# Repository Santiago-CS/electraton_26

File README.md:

# Be Key ITESO Racing Team — Electrical & Embedded Systems

Repositorio central del área de electrónica, sistemas de baja tensión, telemetría y software embebido de **Be Key ITESO Racing Team**, escudería representativa del ITESO en el campeonato nacional **Electratón**.

Este espacio almacena el diseño de hardware (esquemáticos, layouts y archivos de manufactura Gerber/BOM), firmware de unidades de control, protocolos de comunicación en red vehicular e interfaces de adquisición de datos.

---

## 🏎️ Visión General de la Arquitectura

El sistema eléctrico del monoplaza opera bajo una estricta segregación galvánica y funcional entre dos dominios:

1. **Sistema de Alta Tensión (HV - High Voltage):**
   * Banco de celdas de tracción, interruptor general de aislamiento, fusibles de alta corriente y contactores principales.
   * Sistema de Gestión de Baterías (BMS) encargado del balanceo pasivo/activo, monitorización de temperatura por celda y corte seguro ante contingencias.
2. **Sistema de Baja Tensión y Control (LV - Low Voltage):**
   * Lógica de encendido de tracción condicionada a seguridades (*Interlocks*, paro de emergencia/kill switches y frenado hidráulico).
   * Red de comunicación de control y telemetría de parámetros en tiempo real hacia pits.
   * Procesamiento de datos de dinámica, ergonomía e instrumentación del habitáculo del piloto.

---

## 📁 Estructura del Repositorio

```text
├── FRDM-iMX93/
│   ├── 3D Printed Enclosure for FRDM-IMX93/
│   └── FRDM-IMX93-DESIGNFILES/
│       ├── 3D Module/
│       ├── Design Files/
│       ├── Gerbers/
│       └── PDF/
├── docs/                   # Diagramas generales de cableado (harness), pinouts y notas técnicas
├── firmware/               # Proyectos de código fuente embebido (C / C++ / MicroPython)
│   ├── ecu_firmware/       # Lógica principal de tracción y máquina de estados del auto
│   └── wheel_firmware/     # Control del volante, display gráfico e interfaz de mando
├── hardware/               # Diseños electrónicos (Archivos de diseño CAD/EDA, BOMs, Gerbers)
│   ├── ecu/                # PCB de la Unidad de Control del Vehículo (ECU)
│   └── steering_wheel/     # PCB de mandos del volante ergonómico y display de telemetría
└── tools/                  # Scripts de procesamiento, telemetría y configuración en pista
```

---

## 🛠️ Subsistemas de Hardware (Hardware Directory)

### 1. `FRDM-iMX93/`
* **Función:** Plataforma de cómputo embebido y adquisición de datos basada en el procesador NXP i.MX93, empleada para telemetría avanzada, procesamiento y soporte de computación a bordo.
* **Carpetas del módulo:**
  * `3D Printed Enclosure for FRDM-IMX93/`: Archivos de diseño y modelos del gabinete / case para manufactura aditiva y montaje en el chasis.
  * `FRDM-IMX93-DESIGNFILES/`: Archivos de diseño originales de la tarjeta de desarrollo (`3D Module/`, `Design Files/`, `Gerbers/`, `PDF/`).

### 2. `hardware/steering_wheel/`
* **Función:** Módulo de interfaz hombre-máquina (HMI) ubicado en el volante del monoplaza.
* **Componentes Clave:** 
  * Microcontrolador para adquisición de comandos del piloto (pulsadores, selectores rotativos y palancas de cambios/frenado regenerativo).
  * Pantalla gráfica/dashboard integrada para visualización de parámetros críticos en pista (voltaje total, corriente instantánea, velocidad y alarmas del BMS).
  * Comunicación inalámbrica o bus alámbrico hacia la ECU central.
* **Entregables en carpeta:**
  * Esquemáticos y PCB Layout.
  * Archivos Gerber de fabricación y ensamble (CPL/Pick and Place).
  * Lista de materiales (BOM) con números de parte y encapsulados.

### 3. `hardware/ecu/`
* **Función:** Unidad de Control Electrónico encargada de la lógica central del monoplaza y la máquina de estados de seguridad.
* **Componentes Clave:**
  * Microcontrolador principal de gestión en tiempo real.
  * Etapa de acondicionamiento de señales y lectura de sensores analógicos/digitales (posición del pedal de aceleración, presión de frenos, efecto Hall).
  * Drivers y relevadores para control de contactores de potencia y luces reglamentarias de estado (Tractive System Active Light).
  * Circuito de detección de fallas y enlace directo con la línea de paro de emergencia (*Shutdown Circuit*).
* **Entregables en carpeta:**
  * Diseño esquemático y diseño de pista multicapa (separación estricta de planos analógicos y digitales).
  * Archivos de manufactura listos para ensamble y fabricación de PCB.
  * Documentación de conectores y asignación de pines del arnés vehicular.

---

## 🌿 Flujo de Trabajo con Git y Creación de Pull Requests (PR)

Un **Pull Request (PR)** es una solicitud formal para que los líderes del área técnica revisen, validen y aprueben tus cambios antes de mezclarlos con el trabajo de los demás. **Nadie sube cambios directos a la rama `main`.**

### 1. Estructura de Ramas Base
* `main`: Producción oficial. Exclusiva para diseños probados y versiones finales enviadas a manufactura.
* `hardware/dev`: Rama base donde se integran los cambios de circuitos, esquemáticos, PCBs y librerías EDA.
* `firmware/dev`: Rama base para integración de código fuente embebido y librerías de control.
* `tools/dev`: Rama base para scripts de telemetría en pista, procesamiento de datos y utilidades de configuración.
* `docs/general`: Rama base para manuales de taller, diagramas de arnés, pinouts y notas técnicas.

---

### 2. Flujo Completo por Terminal

#### Paso 1: Clonar y actualizar el repositorio local
```bash
git clone <URL_DEL_REPOSITORIO>
cd <NOMBRE_DEL_REPO>
git fetch --all
```

#### Paso 2: Crear tu rama personal de trabajo
Sitúate en la rama base de tu disciplina y crea una rama específica para tu tarea:

* **Si vas a diseñar hardware (esquemático/PCB):**
```bash
git checkout hardware/dev
git pull origin hardware/dev
git checkout -b hardware/nombre-tarea
# Ejemplo: git checkout -b hardware/filtro-alimentacion-ecu
```

* **Si vas a programar firmware:**
```bash
git checkout firmware/dev
git pull origin firmware/dev
git checkout -b firmware/nombre-tarea
# Ejemplo: git checkout -b firmware/lectura-pedal-adc
```

* **Si vas a desarrollar scripts / herramientas / telemetría:**
```bash
git checkout tools/dev
git pull origin tools/dev
git checkout -b tools/nombre-tarea
# Ejemplo: git checkout -b tools/parser-telemetria-serial
```

* **Si vas a actualizar documentación o diagramas:**
```bash
git checkout docs/general
git pull origin docs/general
git checkout -b docs/nombre-tarea
# Ejemplo: git checkout -b docs/diagrama-arnes-potencia
```

#### Paso 3: Guardar cambios y crear commits limpios
Agrega únicamente los archivos pertinentes (esquemáticos, código fuente, scripts, modelos 3D). Evita subir archivos temporales, respaldos locales o cachés de compilación:
```bash
git status
git add hardware/ecu/archivo_modificado.kicad_sch
git commit -m "feat(ecu): agregar diodo de proteccion contra polaridad inversa"
```

*Convenciones de mensajes:*
* `feat(módulo):` nueva función, circuito o subsistema.
* `fix(módulo):` corrección de errores, trazos de PCB o bugs de software.
* `docs(módulo):` diagramas de cableado, notas de conexionado o manuales.
* `tools(módulo):` scripts de adquisición, análisis o utilerías de pista.

#### Paso 4: Subir tu rama a GitHub
```bash
git push -u origin <nombre-completo-de-tu-rama>
# Ejemplo: git push -u origin hardware/filtro-alimentacion-ecu
```

---

### 3. Cómo abrir y procesar el Pull Request (PR)

#### Opción A: Desde la interfaz web de GitHub (Método estándar)
1. Entra al enlace del repositorio en GitHub desde tu navegador.
2. Verás un recuadro amarillo con el botón **"Compare & pull request"**. Haz clic ahí. (Si no aparece, entra a la pestaña **Pull requests** y presiona **New pull request**).
3. **Selección de ramas (Punto crítico):**
   * **Base (izquierda):** Selecciona la rama destino según tu área (`hardware/dev`, `firmware/dev`, `tools/dev` o `docs/general`). **No selecciones `main`** a menos que sea una entrega formal de temporada.
   * **Compare (derecha):** Selecciona tu rama de trabajo personal (`hardware/nombre-tarea`, `firmware/nombre-tarea`, etc.).
4. **Título y Descripción:**
   * Título corto y descriptivo: `feat(ecu): Proteccion contra polaridad inversa y desacoplo`.
   * Descripción: Explica qué problema resuelve, qué pruebas realizaste (simulación, osciloscopio o banco de pruebas) y si modificaste algún componente en la BOM.
5. **Revisores:** En la columna lateral derecha, en **Reviewers**, asigna al **Senior Chief Engineer** o al **Capitán de Área Técnica**.
6. Haz clic en **Create pull request**.

#### Opción B: Desde la terminal usando GitHub CLI (`gh`)
Si tienes instalada la herramienta oficial de GitHub en tu consola:
```bash
# Para hardware apuntando a hardware/dev:
gh pr create --base hardware/dev --title "feat(ecu): proteccion inversa" --body "Se agrega diodo y capacitor de desacoplo en entrada de 12V"

# Para firmware apuntando a firmware/dev:
gh pr create --base firmware/dev --title "feat(pedal): calibracion ADC" --body "Lectura lineal de pedal con debounce y promedio movil"

# Para herramientas apuntando a tools/dev:
gh pr create --base tools/dev --title "feat(telemetria): script de lectura serial" --body "Parser de tramas UART y almacenamiento en CSV"

# Para documentación apuntando a docs/general:
gh pr create --base docs/general --title "docs(arnes): pinout conector principal" --body "Actualizacion de diagrama de pines de alimentacion y sensores"
```

#### Paso 5: ¿Qué pasa si te piden correcciones en la revisión?
No cierres el PR ni generes una nueva rama. Aplica las correcciones en tus archivos locales dentro de tu misma rama de trabajo, guarda los cambios y vuelve a enviar el push:
```bash
git add hardware/ecu/archivo_corregido.kicad_sch
git commit -m "fix(ecu): corregir espaciado de pistas segun observaciones"
git push origin <nombre-completo-de-tu-rama>
```
El Pull Request en GitHub se actualizará automáticamente con el nuevo commit. Cuando los revisores den su visto bueno, realizarán el **Merge** formal hacia la rama de desarrollo correspondiente.

---

## 🔒 Protocolos de Seguridad y Trabajo en Taller

Todo trabajo desarrollado en este repositorio debe respetar de forma obligatoria las normas de seguridad del equipo:

1. **Aislamiento Eléctrico:** Antes de conectar cualquier tarjeta o programador al auto, verifique que la etapa de alta tensión se encuentre físicamente desconectada mediante el *Service Plug* y que el bus de potencia esté descargado a menos de 5 V.
2. **Uso de EPP:** Es mandatorio portar calzado de seguridad, bata de laboratorio y lentes normados durante cualquier sesión de soldadura, maquinado o pruebas dinámicas.
3. **Manejo de Baterías:** Queda prohibido intervenir módulos de acumuladores sin guantes dieléctricos y sin extintores adecuados (CO2 / Clase C / F-500) a la mano y despejados.

---

## 📜 Política de Confidencialidad y NDA

Este repositorio contiene información técnica propietaria, sensible y confidencial de **Be Key ITESO Racing Team**:

* Queda estrictamente prohibido clonar, transferir, duplicar, filtrar o exponer estos esquemáticos, diagramas o código a entidades ajenas al proyecto o a otras escuderías de competencia sin un **Convenio de Colaboración e Intercambio Técnico Oficial** firmado por el Team Principal, la Mesa Directiva y avalado por el responsable del PTI de ITESO.
* Cualquier divulgación deliberada o no autorizada causará la apertura inmediata de un expediente disciplinario, la expulsión definitiva del equipo y el escalamiento a las autoridades académicas y al Comité de Ética del ITESO.

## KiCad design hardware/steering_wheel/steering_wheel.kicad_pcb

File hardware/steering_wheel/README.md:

# Steering wheel controller (RW612) — schematic + placement

Hardware for the Electratón 26 steering wheel: an NXP RW612 (Wi-Fi 6 / BLE) controller
driving a 4" LCD, NeoPixels, two encoders and ten buttons, running from a 1S Li-ion pack
with USB-C charging.

**This folder holds the schematic and the board placement. The board is not routed.**

```
source <your venv>/bin/activate
pip install skidl ortools shapely scipy pymupdf scikit-image ezdxf

python steering_wheel.py                  # netlist + KiCad sheets + bom.csv
python tools/check_sch.py                 # re-reads the sheets, checks every pin
python tools/layout_steering.py place     # placement -> build/placed.kicad_pcb
```

Open `steering_wheel.kicad_pro` in KiCad 10 and press **B** to refill the zones.

> The schematic is **generated** by `steering_wheel.py` (SKiDL). Edit that script and
> re-run it — anything changed directly in Eeschema is lost on the next run. Same for the
> placement: it is code in `tools/layout_steering.py`.

> The sheets here are saved in KiCad 10 format. `tools/kicad_sch_export.py` stamps
> regenerated sheets as KiCad 9 (`version 20250114`, lines 461 and 693), so after re-running
> `steering_wheel.py` KiCad 10 will offer to upgrade them again — harmless, or change those
> two lines to `20260306` / `"10.0"` to stop it.

## State

| | |
|---|---|
| Schematic | rev 0.2 — 5 sheets, 237 parts, 152 nets, **ERC 0 violations** |
| Board | **placed, not routed** — 8 layers, JLCPCB `JLC08161H-7628`, 1.6 mm, 138.9 × 83.8 mm |
| Placement copper | 108 tracks / 17 vias, all locked (power loops, USB breakout, battery trunks, RW612 buck and crystal links) |
| DRC (zones filled, `--schematic-parity`) | **0 errors, 0 parity errors, 384 unconnected** |

The 384 unconnected are the connections still to be routed — exactly what a placement-only
board should report.

## Layer stack

| # | Layer | Use |
|---|---|---|
| 1 | F.Cu | parts (all on top), signals, 50 Ω RF microstrip, GND pour |
| 2 | In1.Cu | **GND plane** — RF and USB reference |
| 3 | In2.Cu | signal |
| 4 | In3.Cu | **+3V3 plane** |
| 5 | In4.Cu | **GND plane** |
| 6 | In5.Cu | signal |
| 7 | In6.Cu | **GND plane** |
| 8 | B.Cu | signals, VSYS_SW trunk, GND pour |

Four routing layers, each against a ground plane. Vias are 0.4/0.2 mm, BGA fan-out
0.35/0.2 mm (8.01:1 aspect ratio — no small-via option needed).

## Routing it

The routing pipeline is not in this folder. A **fully routed** 8-layer version of this same
design (0 DRC errors, 0 parity errors) lives in `~/projects/irt/steering_wheel/pcb_8layer`,
and the 4-layer original in `~/projects/irt/steering_wheel/pcb`. To route from here, copy
`build/env.sh`, `build/run_all.sh`, `build/finalize.sh` and `build/strip_vias.py` from
`pcb_8layer/build/` and fix the paths in `env.sh`.

## Layout

| Path | What |
|---|---|
| `steering_wheel.py` | the design (SKiDL) — **the source of truth** |
| `*.kicad_sch`, `steering_wheel.kicad_pro`, `*-lib-table` | generated KiCad project |
| `steering_wheel.kicad_pcb` | the placed board (copy of `build/placed.kicad_pcb`) |
| `steering_wheel.net`, `bom.csv` | generated netlist and BOM (98 lines, 237 parts, 9 DNP) |
| `lib/` | project symbols and footprints, the stock KiCad symbols used, RW612 ball map |
| `tools/` | schematic export, placement, pre-routing and KiCad-Python helpers |
| `docs/design_notes.md` | **full design documentation** — power tree, pin map, firmware hooks, layout, schematic review, what to check before ordering |
| `docs/PCB_Volante_2026.DXF` | mechanical outline and mounting holes (placement reads this) |
| `docs/pcb_*.png`, `docs/pcb_layers.pdf` | previews of the placed board |
| `build/kicad_netlist.net` | KiCad's own netlist; the board takes no-connect net names from it so DRC parity matches |

## Before ordering

See `docs/design_notes.md` section 7. Two items need a decision:

1. **Q101 (FS8205A) pads 1 and 8** are both the `D12` common-drain pin, which the schematic
   leaves unconnected, so DRC always reports one unconnected item. The usual SOP-8 pinout
   has no drain pin (1,2,3 = S1, 6,7,8 = S2), so the symbol/footprint pin map may be wrong.
2. **The USB pair is ~128 Ω differential, not 90 Ω** on this stackup. ~0.40 mm traces at a
   0.15 mm gap would reach 90 Ω.

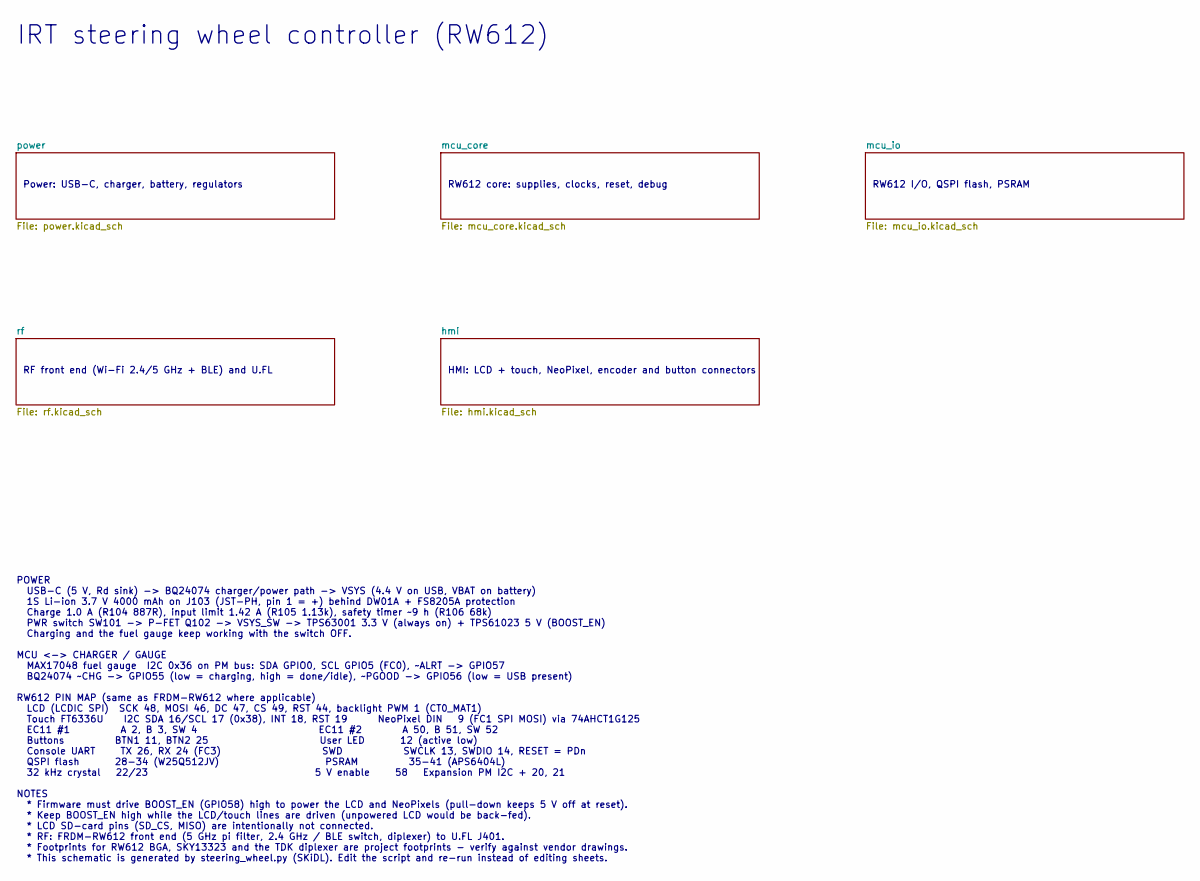
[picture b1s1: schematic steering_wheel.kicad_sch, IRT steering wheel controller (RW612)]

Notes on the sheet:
RW612 I/O, QSPI flash, PSRAM
Power: USB-C, charger, battery, regulators
RW612 core: supplies, clocks, reset, debug
HMI: LCD + touch, NeoPixel, encoder and button connectors
POWER USB-C (5 V, Rd sink) -> BQ24074 charger/power path -> VSYS (4.4 V on USB, VBAT on battery) 1S Li-ion 3.7 V 4000 mAh on J103 (JST-PH, pin 1 = +) behind DW01A + FS8205A protection Charge 1.0 A (R104 887R), input limit 1.42 A (R105 1.13k), safety timer ~9 h (R106 68k) PWR switch SW101 -> P-FET Q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
IRT steering wheel controller (RW612)
RF front end (Wi-Fi 2.4/5 GHz + BLE) and U.FL

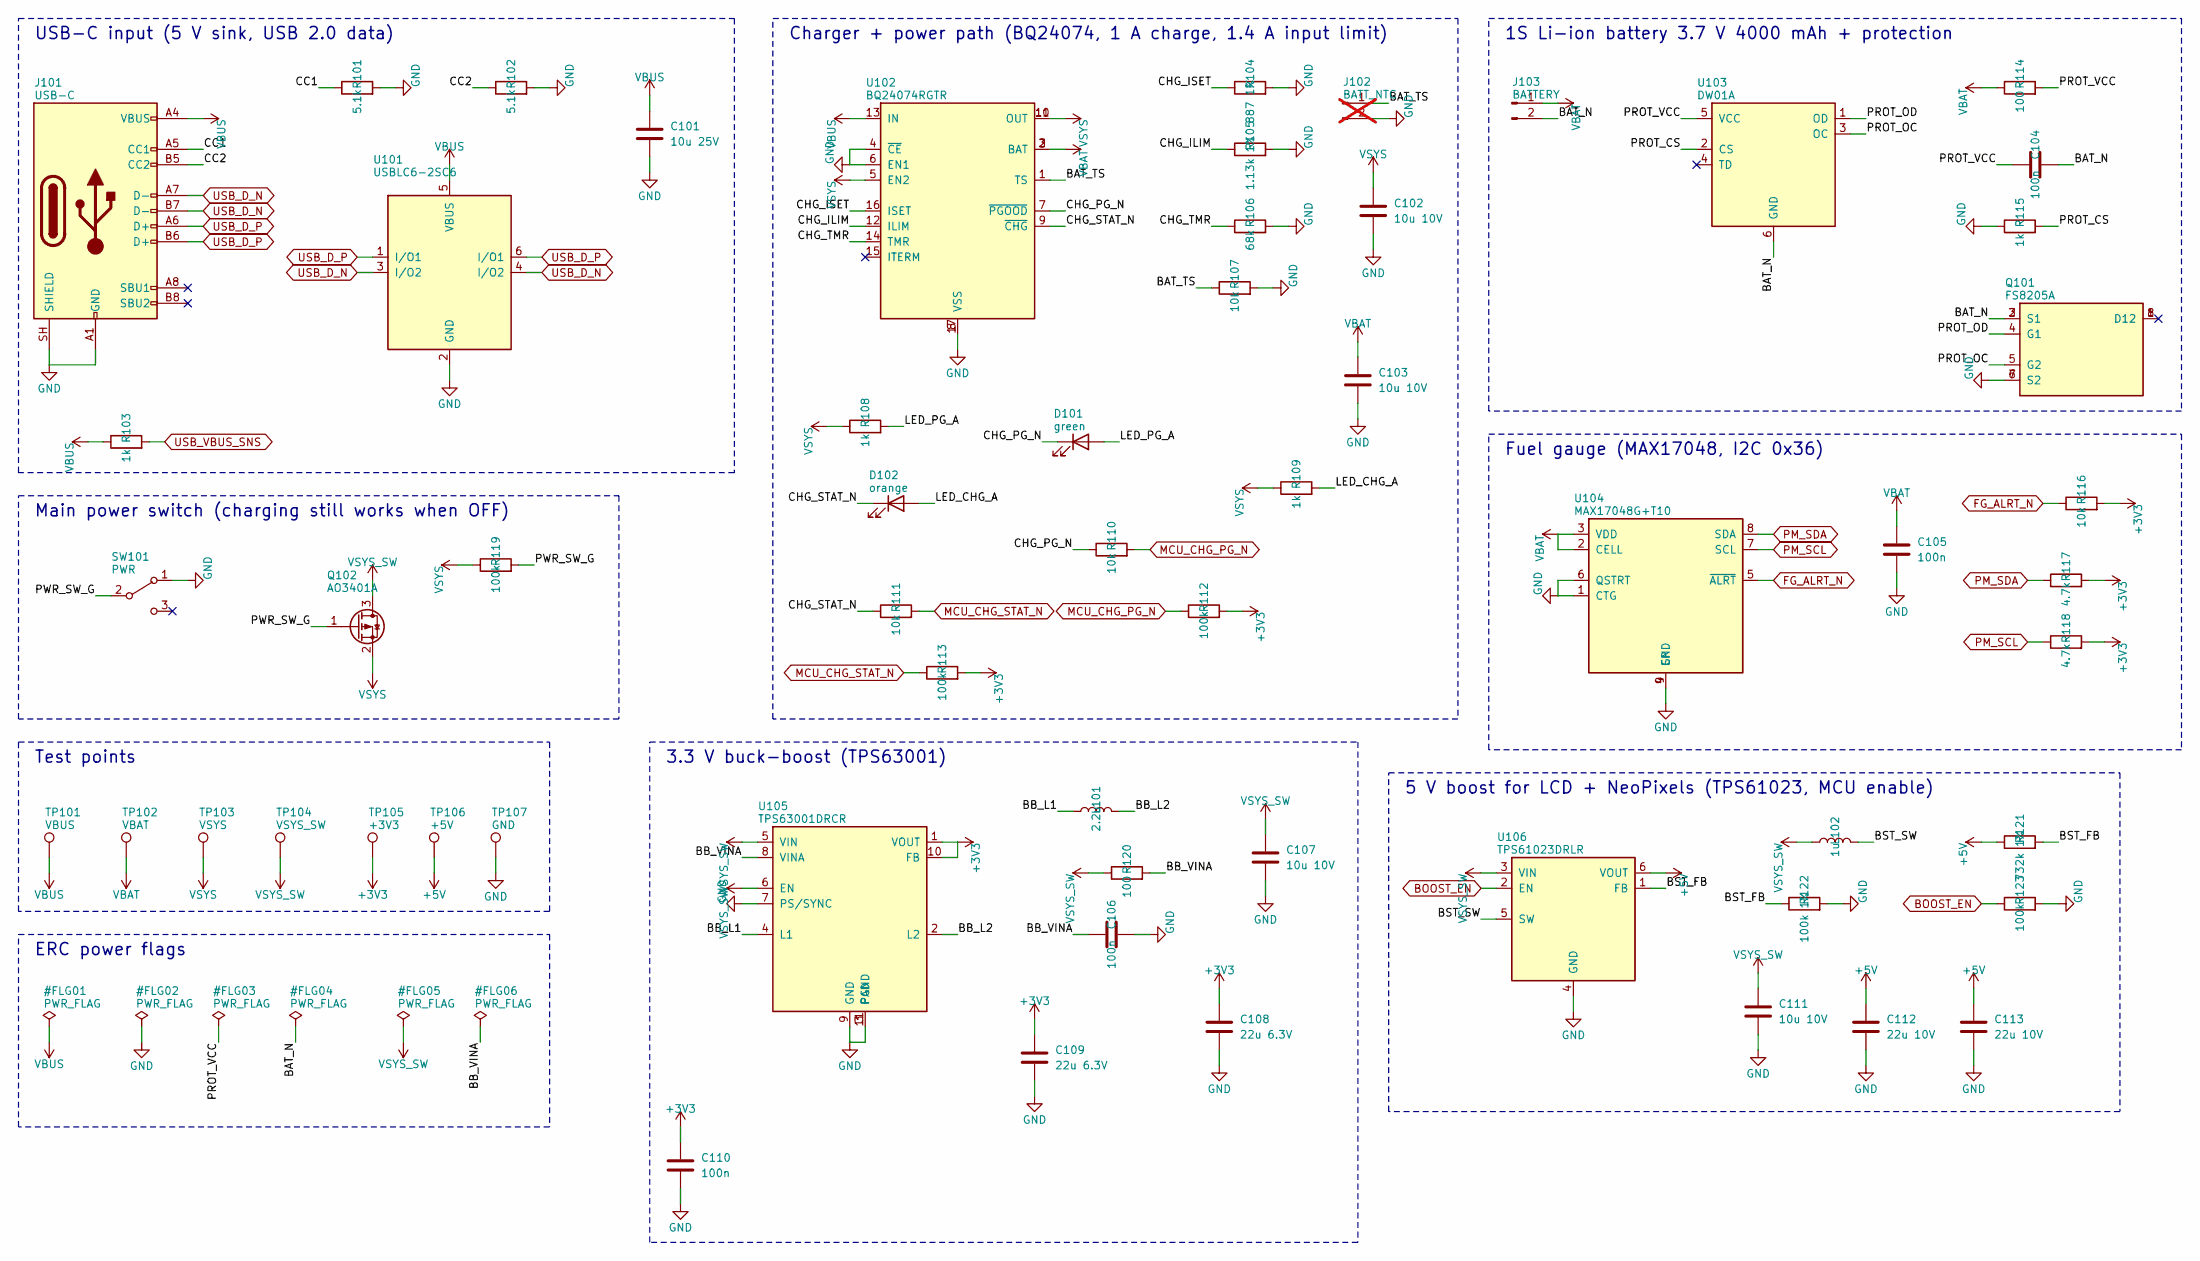
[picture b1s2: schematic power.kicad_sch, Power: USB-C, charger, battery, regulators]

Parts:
C101: 10u 25V; C_0805_2012Metric
C102, C103: 10u 10V; C_0805_2012Metric
C104, C105, C106, C110: 100n; C_0402_1005Metric
C107, C111: 10u 10V; C_0603_1608Metric
C108, C109: 22u 6.3V; C_0805_2012Metric
C112, C113: 22u 10V; C_0805_2012Metric
D101: green; LED_0603_1608Metric; MPN LED green 0603
D102: orange; LED_0603_1608Metric; MPN LED orange 0603
J101: USB-C; USB_C_Receptacle_HRO_TYPE-C-31-M-12; MPN TYPE-C-31-M-12; LCSC C165948
J102: BATT_NTC; PinHeader_1x02_P2.54mm_Vertical; not fitted
J103: BATTERY; JST_PH_S2B-PH-SM4-TB_1x02-1MP_P2.00mm_Horizontal; MPN S2B-PH-SM4-TB; LCSC C295747
L101: 2.2u; L_Wuerth_MAPI-3015; MPN 74438335022
L102: 1u; L_Wuerth_MAPI-4020; MPN 74438357010
Q101: FS8205A; TSSOP-8_4.4x3mm_P0.65mm; MPN FS8205A; LCSC C16052
Q102: AO3401A; SOT-23; MPN AO3401A; LCSC C15127
R101, R102: 5.1k; R_0402_1005Metric
R103, R108, R109, R115: 1k; R_0402_1005Metric
R104: 887 1%; R_0402_1005Metric
R105: 1.13k 1%; R_0402_1005Metric
R106: 68k; R_0402_1005Metric
R107, R110, R111, R116: 10k; R_0402_1005Metric
R112, R113, R119, R123: 100k; R_0402_1005Metric
R114, R120: 100; R_0402_1005Metric
R117, R118: 4.7k; R_0402_1005Metric
R121: 732k 1%; R_0402_1005Metric
R122: 100k 1%; R_0402_1005Metric
SW101: PWR; SW_SPDT_PCM12; MPN PCM12SMTR; LCSC C221841
TP101: VBUS; TestPoint_Pad_D1.0mm
TP102: VBAT; TestPoint_Pad_D1.0mm
TP103: VSYS; TestPoint_Pad_D1.0mm
TP104: VSYS_SW; TestPoint_Pad_D1.0mm
TP105: +3V3; TestPoint_Pad_D1.0mm
TP106: +5V; TestPoint_Pad_D1.0mm
TP107: GND; TestPoint_Pad_D1.0mm
U101: USBLC6-2SC6; SOT-23-6; MPN USBLC6-2SC6; LCSC C7519
U102: BQ24074RGTR; VQFN-16-1EP_3x3mm_P0.5mm_EP1.68x1.68mm; MPN BQ24074RGTR; LCSC C54313
U103: DW01A; SOT-23-6; MPN DW01A; LCSC C351410
U104: MAX17048G+T10; TDFN-8-1EP_2x2mm_P0.5mm_EP0.8x1.2mm; MPN MAX17048G+T10; LCSC C2682616
U105: TPS63001DRCR; VSON-10-1EP_3x3mm_P0.5mm_EP1.65x2.4mm; MPN TPS63001DRCR; LCSC C28060
U106: TPS61023DRLR; SOT-563; MPN TPS61023DRLR; LCSC C919459

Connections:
+3V3: C108.1, C109.1, C110.1, R112.2, R113.2, R116.2, R117.2, R118.2, TP105.1, U105.1 (VOUT), U105.10 (FB); also elsewhere on the board
+5V: C112.1, C113.1, R121.1, TP106.1, U106.6 (VOUT); also elsewhere on the board
/power/BAT_N: C104.2, J103.2, Q101.2 (S1), Q101.3 (S1), U103.6 (GND)
/power/BAT_TS: J102.1, R107.1, U102.1 (TS)
/power/BB_L1: L101.1, U105.4 (L1)
/power/BB_L2: L101.2, U105.2 (L2)
/power/BB_VINA: C106.1, R120.2, U105.8 (VINA)
/power/BST_FB: R121.2, R122.1, U106.1 (FB)
/power/BST_SW: L102.2, U106.5 (SW)
/power/CC1: J101.A5 (CC1), R101.1
/power/CC2: J101.B5 (CC2), R102.1
/power/CHG_ILIM: R105.1, U102.12 (ILIM)
/power/CHG_ISET: R104.1, U102.16 (ISET)
/power/CHG_PG_N: D101.1 (K), R110.1, U102.7 (~PGOOD)
/power/CHG_STAT_N: D102.1 (K), R111.1, U102.9 (~CHG)
/power/CHG_TMR: R106.1, U102.14 (TMR)
/power/LED_CHG_A: D102.2 (A), R109.2
/power/LED_PG_A: D101.2 (A), R108.2
/power/PROT_CS: R115.2, U103.2 (CS)
/power/PROT_OC: Q101.5 (G2), U103.3 (OC)
/power/PROT_OD: Q101.4 (G1), U103.1 (OD)
/power/PROT_VCC: C104.1, R114.2, U103.5 (VCC)
/power/PWR_SW_G: Q102.1 (G), R119.2, SW101.2 (B)
BOOST_EN: R123.1, U106.2 (EN); also elsewhere on the board
FG_ALRT_N: R116.1, U104.5 (~ALRT); also elsewhere on the board
GND: C101.2, C102.2, C103.2, C105.2, C106.2, C107.2, C108.2, C109.2, C110.2, C111.2, C112.2, C113.2, J101.A1 (GND), J101.A12 (GND), J101.B1 (GND), J101.B12 (GND), J101.SH (SHIELD), J102.2, Q101.6 (S2), Q101.7 (S2), R101.2, R102.2, R104.2, R105.2, R106.2, R107.2, R115.1, R122.2, R123.2, SW101.1 (A), TP107.1, U101.2 (GND), U102.4 (~CE), U102.6 (EN1), U102.8 (VSS), U102.17 (VSS), U104.1 (CTG), U104.4 (GND), U104.6 (QSTRT), U104.9 (EP), U105.3 (PGND), U105.7 (PS/SYNC), U105.9 (GND), U105.11 (PAD), U106.4 (GND); also elsewhere on the board
MCU_CHG_PG_N: R110.2, R112.1; also elsewhere on the board
MCU_CHG_STAT_N: R111.2, R113.1; also elsewhere on the board
PM_SCL: R118.1, U104.7 (SCL); also elsewhere on the board
PM_SDA: R117.1, U104.8 (SDA); also elsewhere on the board
USB_D_N: J101.A7 (D-), J101.B7 (D-), U101.3 (I/O2), U101.4 (I/O2); also elsewhere on the board
USB_D_P: J101.A6 (D+), J101.B6 (D+), U101.1 (I/O1), U101.6 (I/O1); also elsewhere on the board
USB_VBUS_SNS: R103.2; also elsewhere on the board
VBAT: C103.1, C105.1, J103.1, R114.1, TP102.1, U102.2 (BAT), U102.3 (BAT), U104.2 (CELL), U104.3 (VDD)
VBUS: C101.1, J101.A4 (VBUS), J101.A9 (VBUS), J101.B4 (VBUS), J101.B9 (VBUS), R103.1, TP101.1, U101.5 (VBUS), U102.13 (IN)
VSYS: C102.1, Q102.2 (S), R108.1, R109.1, R119.1, TP103.1, U102.5 (EN2), U102.10 (OUT), U102.11 (OUT)
VSYS_SW: C107.1, C111.1, L102.1, Q102.3 (D), R120.1, TP104.1, U105.5 (VIN), U105.6 (EN), U106.3 (VIN)

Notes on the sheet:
Test points
Fuel gauge (MAX17048, I2C 0x36)
5 V boost for LCD + NeoPixels (TPS61023, MCU enable)
Charger + power path (BQ24074, 1 A charge, 1.4 A input limit)
1S Li-ion battery 3.7 V 4000 mAh + protection
3.3 V buck-boost (TPS63001)
ERC power flags
Main power switch (charging still works when OFF)
USB-C input (5 V sink, USB 2.0 data)

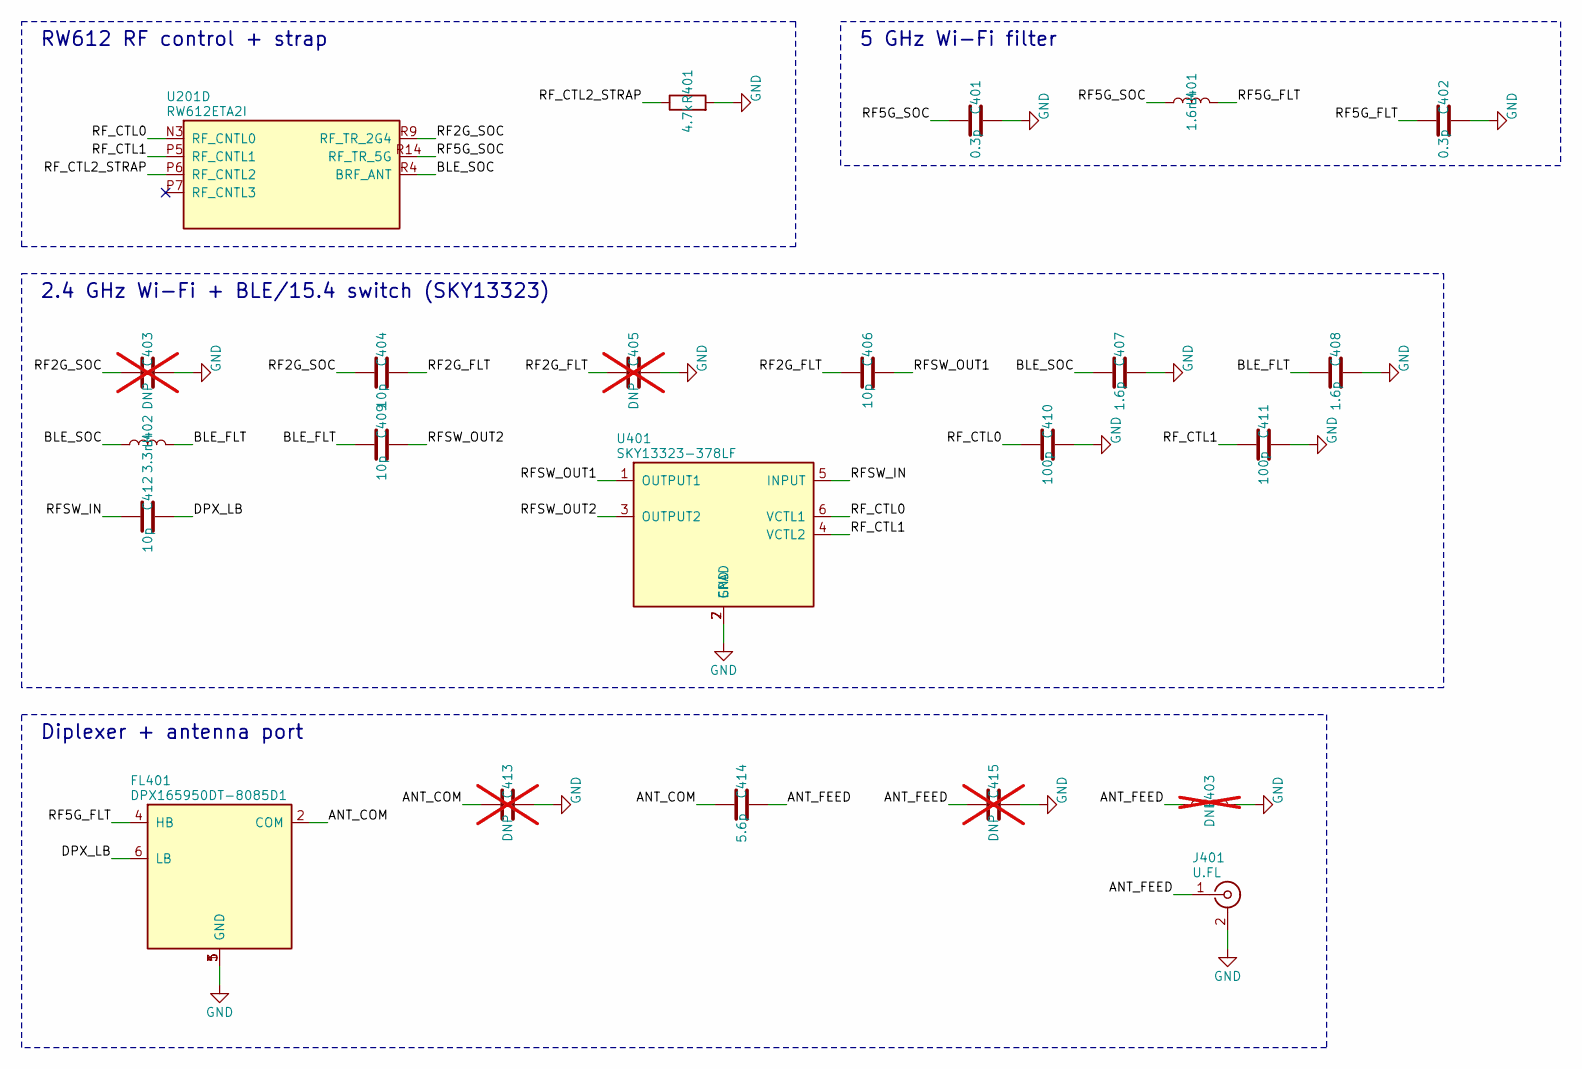
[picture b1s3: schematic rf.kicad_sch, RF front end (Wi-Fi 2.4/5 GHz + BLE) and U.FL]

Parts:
C401, C402: 0.3p; C_0201_0603Metric
C403, C405, C413, C415: DNP; C_0201_0603Metric; not fitted
C404, C406, C409, C412: 10p; C_0201_0603Metric
C407, C408: 1.6p; C_0201_0603Metric
C410, C411: 100p; C_0201_0603Metric
C414: 5.6p; C_0201_0603Metric
FL401: DPX165950DT-8085D1; TDK_DPX165950DT_1608_6T; MPN DPX165950DT-8085D1
J401: U.FL; U.FL_Hirose_U.FL-R-SMT-1_Vertical; MPN U.FL-R-SMT-1(10); LCSC C88373
L401: 1.6nH; L_0201_0603Metric; MPN LQP03TN1N6B02D
L402: 3.3nH; L_0201_0603Metric; MPN LQP03TN3N3B02D
L403: DNP; L_0201_0603Metric; not fitted
R401: 4.7k; R_0402_1005Metric
U201: RW612ETA2I; NXP_TFBGA145_8x8mm_P0.5mm; MPN RW612ETA2I
U401: SKY13323-378LF; Skyworks_MLPD-6-1EP_1x1mm; MPN SKY13323-378LF; LCSC C150867

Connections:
/rf/ANT_COM: C413.1, C414.1, FL401.2 (COM)
/rf/ANT_FEED: C414.2, C415.1, J401.1 (In), L403.1
/rf/BLE_FLT: C408.1, C409.1, L402.2
/rf/BLE_SOC: C407.1, L402.1, U201.R4 (BRF_ANT)
/rf/DPX_LB: C412.2, FL401.6 (LB)
/rf/RF2G_FLT: C404.2, C405.1, C406.1
/rf/RF2G_SOC: C403.1, C404.1, U201.R9 (RF_TR_2G4)
/rf/RF5G_FLT: C402.1, FL401.4 (HB), L401.2
/rf/RF5G_SOC: C401.1, L401.1, U201.R14 (RF_TR_5G)
/rf/RFSW_IN: C412.1, U401.5 (INPUT)
/rf/RFSW_OUT1: C406.2, U401.1 (OUTPUT1)
/rf/RFSW_OUT2: C409.2, U401.3 (OUTPUT2)
/rf/RF_CTL0: C410.1, U201.N3 (RF_CNTL0), U401.6 (VCTL1)
/rf/RF_CTL1: C411.1, U201.P5 (RF_CNTL1), U401.4 (VCTL2)
/rf/RF_CTL2_STRAP: R401.1, U201.P6 (RF_CNTL2)
GND: C401.2, C402.2, C403.2, C405.2, C407.2, C408.2, C410.2, C411.2, C413.2, C415.2, FL401.1 (GND), FL401.3 (GND), FL401.5 (GND), J401.2 (Ext), L403.2, R401.2, U401.2 (GND), U401.7 (EPAD); also elsewhere on the board

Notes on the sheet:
RW612 RF control + strap
2.4 GHz Wi-Fi + BLE/15.4 switch (SKY13323)
Diplexer + antenna port
5 GHz Wi-Fi filter

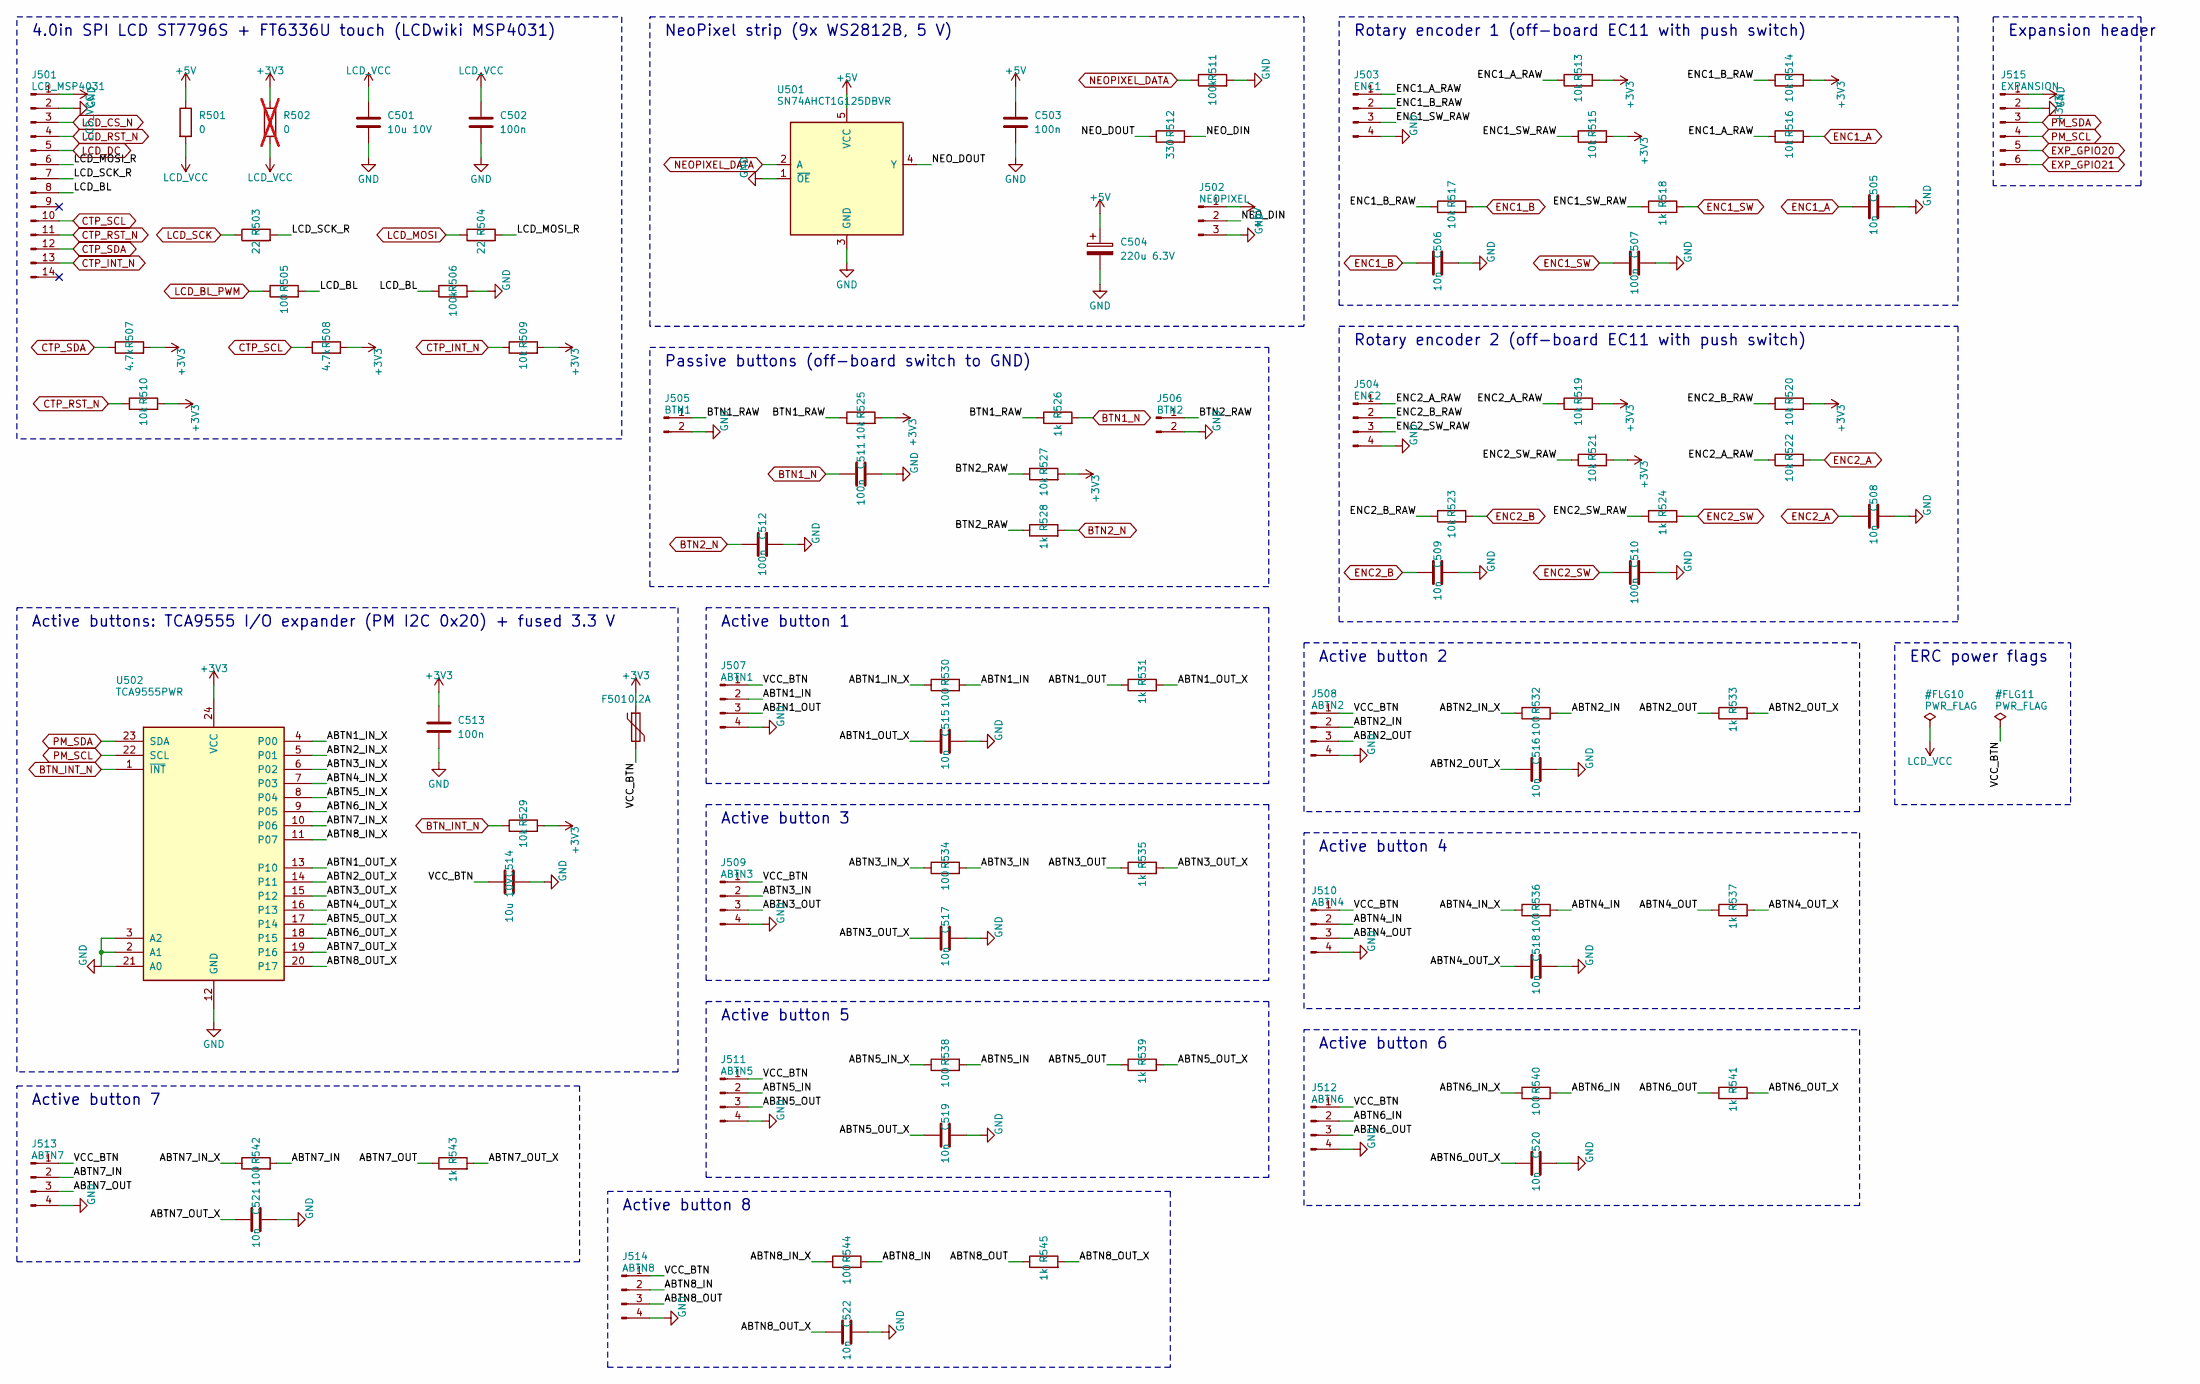
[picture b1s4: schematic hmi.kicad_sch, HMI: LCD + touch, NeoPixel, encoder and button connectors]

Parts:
C501, C514: 10u 10V; C_0603_1608Metric
C502, C503, C507, C510, C511, C512, C513: 100n; C_0402_1005Metric
C504: 220u 6.3V; CP_Elec_6.3x5.4
C505, C506, C508, C509, C515, C516, C517, C518, C519, C520, C521, C522: 10n; C_0402_1005Metric
F501: 0.2A; Fuse_1206_3216Metric; MPN 1206L020YR; LCSC C207035
J501: LCD_MSP4031; JST_PH_B14B-PH-K_1x14_P2.00mm_Vertical; MPN B14B-PH-K-S(LF)(SN); LCSC C158024
J502: NEOPIXEL; JST_XH_B3B-XH-A_1x03_P2.50mm_Vertical; MPN B3B-XH-A
J503: ENC1; JST_PH_B4B-PH-K_1x04_P2.00mm_Vertical; MPN B4B-PH-K-S(LF)(SN); LCSC C131334
J504: ENC2; JST_PH_B4B-PH-K_1x04_P2.00mm_Vertical; MPN B4B-PH-K-S(LF)(SN); LCSC C131334
J505: BTN1; JST_PH_B2B-PH-K_1x02_P2.00mm_Vertical; MPN B2B-PH-K-S(LF)(SN); LCSC C131337
J506: BTN2; JST_PH_B2B-PH-K_1x02_P2.00mm_Vertical; MPN B2B-PH-K-S(LF)(SN); LCSC C131337
J507: ABTN1; JST_PH_B4B-PH-K_1x04_P2.00mm_Vertical; MPN B4B-PH-K-S(LF)(SN); LCSC C131334
J508: ABTN2; JST_PH_B4B-PH-K_1x04_P2.00mm_Vertical; MPN B4B-PH-K-S(LF)(SN); LCSC C131334
J509: ABTN3; JST_PH_B4B-PH-K_1x04_P2.00mm_Vertical; MPN B4B-PH-K-S(LF)(SN); LCSC C131334
J510: ABTN4; JST_PH_B4B-PH-K_1x04_P2.00mm_Vertical; MPN B4B-PH-K-S(LF)(SN); LCSC C131334
J511: ABTN5; JST_PH_B4B-PH-K_1x04_P2.00mm_Vertical; MPN B4B-PH-K-S(LF)(SN); LCSC C131334
J512: ABTN6; JST_PH_B4B-PH-K_1x04_P2.00mm_Vertical; MPN B4B-PH-K-S(LF)(SN); LCSC C131334
J513: ABTN7; JST_PH_B4B-PH-K_1x04_P2.00mm_Vertical; MPN B4B-PH-K-S(LF)(SN); LCSC C131334
J514: ABTN8; JST_PH_B4B-PH-K_1x04_P2.00mm_Vertical; MPN B4B-PH-K-S(LF)(SN); LCSC C131334
J515: EXPANSION; PinHeader_1x06_P2.54mm_Vertical
R501: 0; R_0603_1608Metric
R502: 0; R_0603_1608Metric; not fitted
R503, R504: 22; R_0402_1005Metric
R505, R530, R532, R534, R536, R538, R540, R542, R544: 100; R_0402_1005Metric
R506, R511: 100k; R_0402_1005Metric
R507, R508: 4.7k; R_0402_1005Metric
R509, R510, R513, R514, R515, R516, R517, R519, R520, R521, R522, R523, R525, R527, R529: 10k; R_0402_1005Metric
R512: 330; R_0402_1005Metric
R518, R524, R526, R528, R531, R533, R535, R537, R539, R541, R543, R545: 1k; R_0402_1005Metric
U501: SN74AHCT1G125DBVR; SOT-23-5; MPN SN74AHCT1G125DBVR; LCSC C7484
U502: TCA9555PWR; TSSOP-24_4.4x7.8mm_P0.65mm; MPN TCA9555PWR; LCSC C465732

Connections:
+3V3: C513.1, F501.1, J515.1, R502.1, R507.2, R508.2, R509.2, R510.2, R513.2, R514.2, R515.2, R519.2, R520.2, R521.2, R525.2, R527.2, R529.2, U502.24 (VCC); also elsewhere on the board
+5V: C503.1, C504.1, J502.1, R501.1, U501.5 (VCC); also elsewhere on the board
/hmi/ABTN1_IN: J507.2, R530.2
/hmi/ABTN1_IN_X: R530.1, U502.4 (P00)
/hmi/ABTN1_OUT: J507.3, R531.1
/hmi/ABTN1_OUT_X: C515.1, R531.2, U502.13 (P10)
/hmi/ABTN2_IN: J508.2, R532.2
/hmi/ABTN2_IN_X: R532.1, U502.5 (P01)
/hmi/ABTN2_OUT: J508.3, R533.1
/hmi/ABTN2_OUT_X: C516.1, R533.2, U502.14 (P11)
/hmi/ABTN3_IN: J509.2, R534.2
/hmi/ABTN3_IN_X: R534.1, U502.6 (P02)
/hmi/ABTN3_OUT: J509.3, R535.1
/hmi/ABTN3_OUT_X: C517.1, R535.2, U502.15 (P12)
/hmi/ABTN4_IN: J510.2, R536.2
/hmi/ABTN4_IN_X: R536.1, U502.7 (P03)
/hmi/ABTN4_OUT: J510.3, R537.1
/hmi/ABTN4_OUT_X: C518.1, R537.2, U502.16 (P13)
/hmi/ABTN5_IN: J511.2, R538.2
/hmi/ABTN5_IN_X: R538.1, U502.8 (P04)
/hmi/ABTN5_OUT: J511.3, R539.1
/hmi/ABTN5_OUT_X: C519.1, R539.2, U502.17 (P14)
/hmi/ABTN6_IN: J512.2, R540.2
/hmi/ABTN6_IN_X: R540.1, U502.9 (P05)
/hmi/ABTN6_OUT: J512.3, R541.1
/hmi/ABTN6_OUT_X: C520.1, R541.2, U502.18 (P15)
/hmi/ABTN7_IN: J513.2, R542.2
/hmi/ABTN7_IN_X: R542.1, U502.10 (P06)
/hmi/ABTN7_OUT: J513.3, R543.1
/hmi/ABTN7_OUT_X: C521.1, R543.2, U502.19 (P16)
/hmi/ABTN8_IN: J514.2, R544.2
/hmi/ABTN8_IN_X: R544.1, U502.11 (P07)
/hmi/ABTN8_OUT: J514.3, R545.1
/hmi/ABTN8_OUT_X: C522.1, R545.2, U502.20 (P17)
/hmi/BTN1_RAW: J505.1, R525.1, R526.1
/hmi/BTN2_RAW: J506.1, R527.1, R528.1
/hmi/ENC1_A_RAW: J503.1, R513.1, R516.1
/hmi/ENC1_B_RAW: J503.2, R514.1, R517.1
/hmi/ENC1_SW_RAW: J503.3, R515.1, R518.1
/hmi/ENC2_A_RAW: J504.1, R519.1, R522.1
/hmi/ENC2_B_RAW: J504.2, R520.1, R523.1
/hmi/ENC2_SW_RAW: J504.3, R521.1, R524.1
/hmi/LCD_BL: J501.8, R505.2, R506.1
/hmi/LCD_MOSI_R: J501.6, R504.2
/hmi/LCD_SCK_R: J501.7, R503.2
/hmi/NEO_DIN: J502.2, R512.2
/hmi/NEO_DOUT: R512.1, U501.4 (Y)
/hmi/VCC_BTN: C514.1, F501.2, J507.1, J508.1, J509.1, J510.1, J511.1, J512.1, J513.1, J514.1
BTN1_N: C511.1, R526.2; also elsewhere on the board
BTN2_N: C512.1, R528.2; also elsewhere on the board
BTN_INT_N: R529.1, U502.1 (~INT); also elsewhere on the board
CTP_INT_N: J501.13, R509.1; also elsewhere on the board
CTP_RST_N: J501.11, R510.1; also elsewhere on the board
CTP_SCL: J501.10, R508.1; also elsewhere on the board
CTP_SDA: J501.12, R507.1; also elsewhere on the board
ENC1_A: C505.1, R516.2; also elsewhere on the board
ENC1_B: C506.1, R517.2; also elsewhere on the board
ENC1_SW: C507.1, R518.2; also elsewhere on the board
ENC2_A: C508.1, R522.2; also elsewhere on the board
ENC2_B: C509.1, R523.2; also elsewhere on the board
ENC2_SW: C510.1, R524.2; also elsewhere on the board
EXP_GPIO20: J515.5; also elsewhere on the board
EXP_GPIO21: J515.6; also elsewhere on the board
GND: C501.2, C502.2, C503.2, C504.2, C505.2, C506.2, C507.2, C508.2, C509.2, C510.2, C511.2, C512.2, C513.2, C514.2, C515.2, C516.2, C517.2, C518.2, C519.2, C520.2, C521.2, C522.2, J501.2, J502.3, J503.4, J504.4, J505.2, J506.2, J507.4, J508.4, J509.4, J510.4, J511.4, J512.4, J513.4, J514.4, J515.2, R506.2, R511.2, U501.1 (~OE), U501.3 (GND), U502.2 (A1), U502.3 (A2), U502.12 (GND), U502.21 (A0); also elsewhere on the board
LCD_BL_PWM: R505.1; also elsewhere on the board
LCD_CS_N: J501.3; also elsewhere on the board
LCD_DC: J501.5; also elsewhere on the board
LCD_MOSI: R504.1; also elsewhere on the board
LCD_RST_N: J501.4; also elsewhere on the board
LCD_SCK: R503.1; also elsewhere on the board
LCD_VCC: C501.1, C502.1, J501.1, R501.2, R502.2
NEOPIXEL_DATA: R511.1, U501.2 (A); also elsewhere on the board
PM_SCL: J515.4, U502.22 (SCL); also elsewhere on the board
PM_SDA: J515.3, U502.23 (SDA); also elsewhere on the board

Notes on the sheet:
Active button 2
Passive buttons (off-board switch to GND)
Active buttons: TCA9555 I/O expander (PM I2C 0x20) + fused 3.3 V
Active button 1
ERC power flags
NeoPixel strip (9x WS2812B, 5 V)
4.0in SPI LCD ST7796S + FT6336U touch (LCDwiki MSP4031)
Active button 3
Expansion header
Rotary encoder 1 (off-board EC11 with push switch)
Rotary encoder 2 (off-board EC11 with push switch)
Active button 7
Active button 4
Active button 6
Active button 5
Active button 8
